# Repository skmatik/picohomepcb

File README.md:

# picohomepcb
Raspberry Pi Pico Home Automation - PCB

## Schematics

## PCB

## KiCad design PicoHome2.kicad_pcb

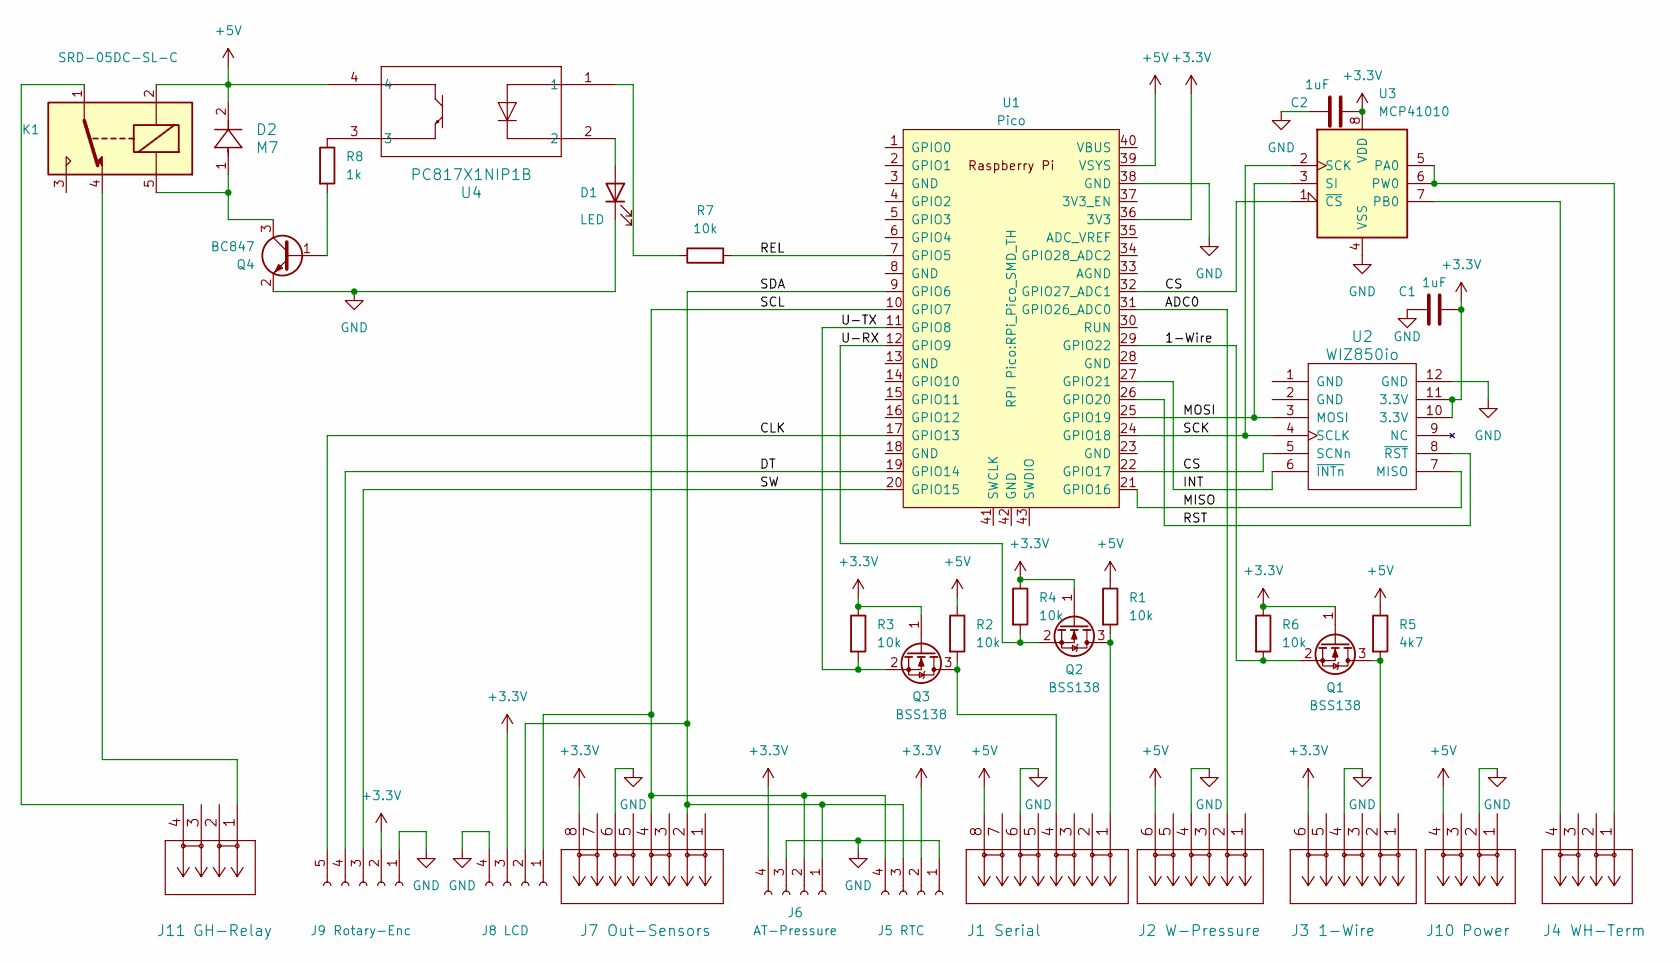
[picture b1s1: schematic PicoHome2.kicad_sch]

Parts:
C1, C2: 1uF; C_0805_2012Metric_Pad1.18x1.45mm_HandSolder
D1: LED; LED_1206_3216Metric_Pad1.42x1.75mm_HandSolder
D2: M7; SMA&slash_DO-214AC_DTC
J1: Serial; 233-504
J2: W-Pressure; 233-503
J3: 1-Wire; 233-503
J4: WH-Term; 233-502
J5: RTC; PinHeader_1x04_P2.54mm_Vertical
J6: AT-Pressure; PinHeader_1x04_P2.54mm_Vertical
J7: Out-Sensors; 233-504
J8: LCD; PinSocket_1x04_P2.54mm_Vertical
J9: Rotary-Enc; PinSocket_1x05_P2.54mm_Vertical
J10: Power; 233-502
J11: GH-Relay; 233-502
K1: SRD-05DC-SL-C; Relay_SPDT_SANYOU_SRD_Series_Form_C
Q1, Q2, Q3: BSS138; SOT-23
Q4: BC847; SOT-23
R1, R2, R3, R4, R6, R7: 10k; R_1206_3216Metric_Pad1.30x1.75mm_HandSolder
R5: 4k7; R_1206_3216Metric_Pad1.30x1.75mm_HandSolder
R8: 1k; R_1206_3216Metric_Pad1.30x1.75mm_HandSolder
U1: Pico; RPi_Pico_SMD_TH
U2: WIZ850io
U3: MCP41010; SOIC8-N_MC_MCH
U4: PC817X1NIP1B; PC817XI_SHP

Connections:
+3.3V: C1.2, C2.2, J3.6, J5.2, J6.4, J7.8, J8.3, J9.2, Q1.1 (G), Q2.1 (G), Q3.1 (G), R3.1, R4.1, R6.1, U1.36 (3V3), U2.10 (3.3V), U2.11 (3.3V), U3.8 (VDD)
+5V: D2.2, J1.8, J2.6, J10.4, K1.2, R1.1, R2.1, R5.1, U1.39 (VSYS), U4.4
/1-Wire: Q1.2 (S), R6.2, U1.29 (GPIO22)
/ADC0: J2.2, U1.31 (GPIO26_ADC0)
/CLK: J9.5, U1.17 (GPIO13)
/CS: U1.22 (GPIO17), U1.32 (GPIO27_ADC1), U2.5 (SCNn), U3.1 (~CS)
/DT: J9.4, U1.19 (GPIO14)
/INT: U1.27 (GPIO21), U2.6 (~INTn)
/MISO: U1.21 (GPIO16), U2.7 (MISO)
/MOSI: U1.25 (GPIO19), U2.3 (MOSI), U3.3 (SI)
/REL: R7.2, U1.7 (GPIO5)
/RST: U1.26 (GPIO20), U2.8 (~RST)
/SCK: U1.24 (GPIO18), U2.4 (SCLK), U3.2 (SCK)
/SCL: J5.4, J6.2, J7.4, J8.1, U1.10 (GPIO7)
/SDA: J5.3, J6.1, J7.2, J8.2, U1.9 (GPIO6)
/SW: J9.3, U1.20 (GPIO15)
/U-RX: Q2.2 (S), R4.2, U1.12 (GPIO9)
/U-TX: Q3.2 (S), R3.2, U1.11 (GPIO8)
GND: C1.1, C2.1, D1.1 (K), J1.6, J2.4, J3.4, J5.1, J6.3, J7.6, J8.4, J9.1, J10.2, Q4.2 (E), U1.38 (GND), U2.12 (GND), U3.4 (VSS)
unnamed: D1.2 (A), U4.2
unnamed: J11.1, K1.4
unnamed: J11.4, K1.1
unnamed: J3.2, Q1.3 (D), R5.2
unnamed: J1.1, Q2.3 (D), R1.2
unnamed: J1.4, Q3.3 (D), R2.2
unnamed: Q4.1 (B), R8.2
unnamed: D2.1, K1.5, Q4.3 (C)
unnamed: R7.1, U4.1
unnamed: R8.1, U4.3
unnamed: J4.1, U3.5 (PA0), U3.6 (PW0)
unnamed: J4.4, U3.7 (PB0)

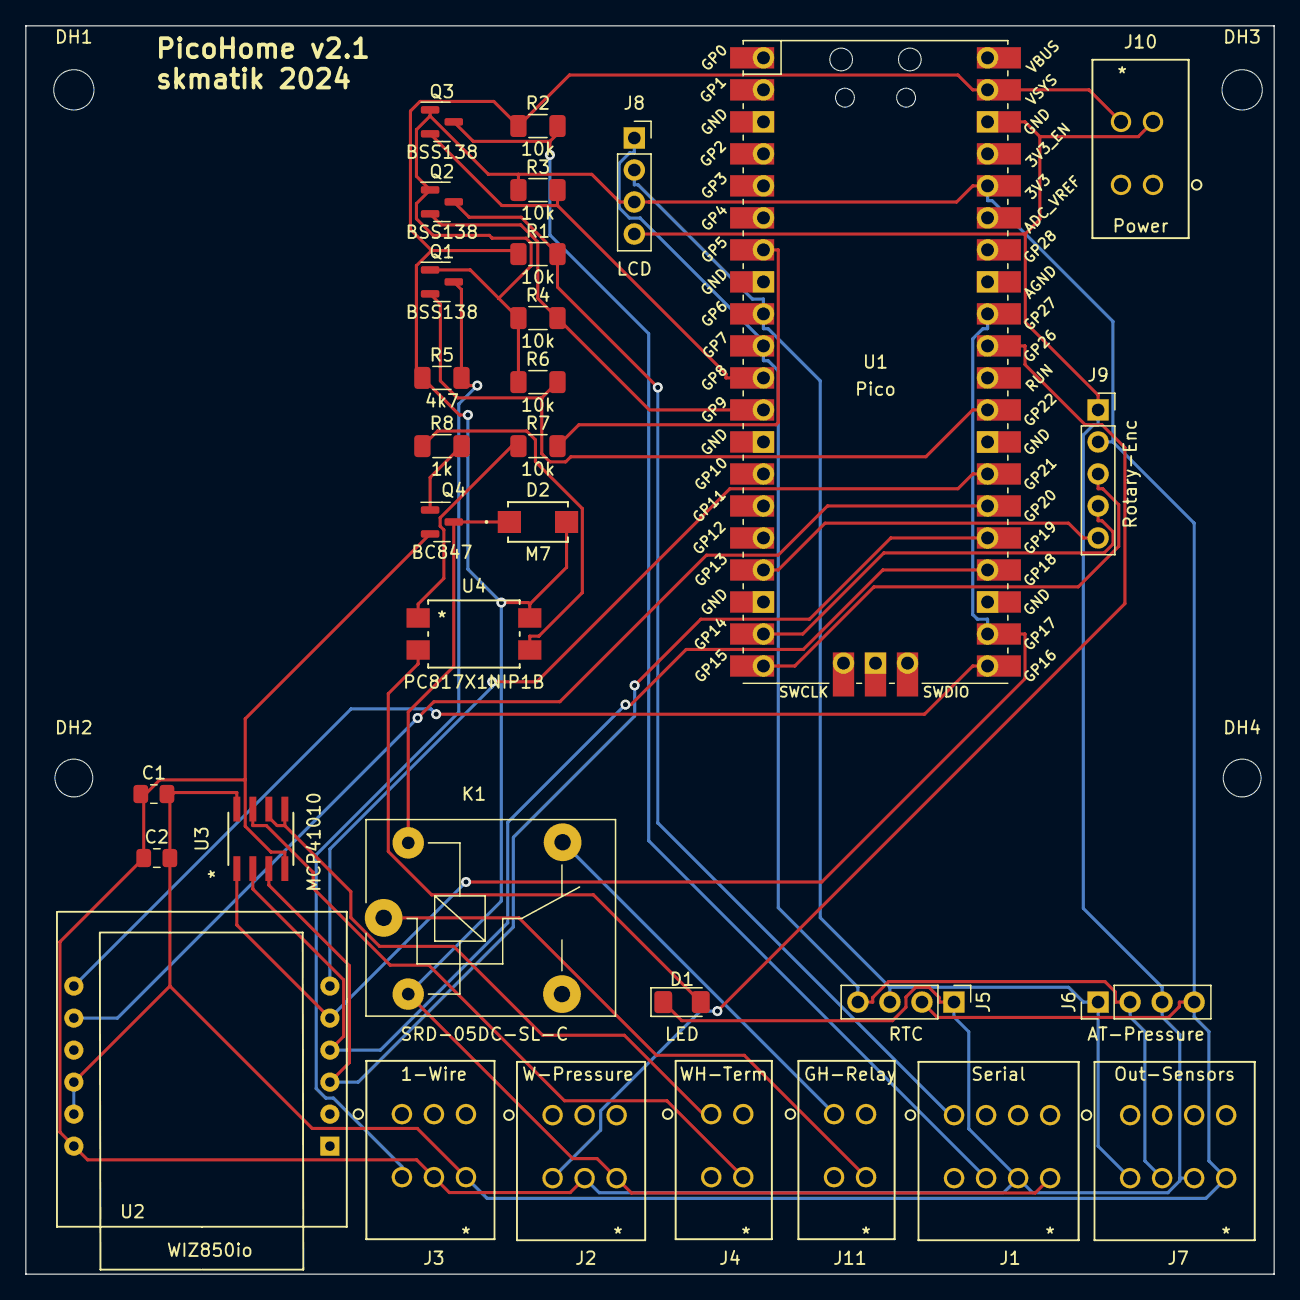
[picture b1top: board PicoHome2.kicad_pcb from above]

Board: 2 copper layers, 99.1 x 99.1 mm, 36 parts (0 on the bottom side), 31 nets.

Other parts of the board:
DH1: DH1; MountingHole_3.2mm_M3
DH2: DH2; MountingHole_3mm
DH3: DH3; MountingHole_3.2mm_M3
DH4: DH4; MountingHole_3mm

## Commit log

2024-10-28 Initial version of PCB

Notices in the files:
parts and their libraries:
Copyright 2016 Accelerated Designs. All rights reserved.
